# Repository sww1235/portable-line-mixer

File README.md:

# portable-line-mixer
A compact line level audio mixer.

Volume control via Digipots.

## TODO

-   Export BOM and price out parts
-   CODE

## Extra parts

-   772-E25-103RYY1 norcomp db25 IP67 connector male
-   772-E25-203RYY1 norcomp db25 IP67 connector female (for panelmount)
-   967-025-010R011 norcomp db25 IP67 backshell for cable
-   SFP6725 norcomp adhesive seal db25 size
-   967-025-CAP norcomp ip67 sealing cap
-   160-067-004R034 norcomp db25 hardware kit
-   767KS1(X) 0.084 \[2.1\] id/od sealed locking power plug switchcraft
-   L722AS 0.08 \[2.0\] id/od sealed locking power jack switchcraft (these sizes are compatible with high amperage version)
-   JCAP  power jack cover
-   35FM3AULS - Sealed locking 3.5mm panel mount jack switchcraft
-   35HDLBAU(S) 3.5mm sealed locking plug switchcraft (S=0.175 diameter cable, no S=0.29 diameter cable)
-   NE8FDX-P6-W IP rated ethercon connector Cat6A shielded neutrik
-   NE8MX6 Cat6A ethercon cable connector neutrik

## Max Power Consumption figures

| Component | Quantity | Current  | Voltage    | Total Watts     |
|:----------|:---------|:---------|:-----------|:----------------|
| 4x Op Amp | 1        | 2.8mA    | ±12V       | 67.2mW          |
| digipots  | 8        | 2uA, 5uA | +5VD, ±5VA | 0.48mW -> 0.5mW |
| microproc | 1        | 27mA     | 5V         | 135mW           |
| Total     |          |          |            | 202.68mW        |
| ref total |          |          |            | 500mW           |

## References / sources

### Code
-   <http://playground.arduino.cc/Main/RotaryEncoders#Example1>
-   <https://www.arduino.cc/en/Reference/Wire>
-   <http://gammon.com.au/interrupts>
-   <https://www.arduino.cc/en/Reference/AttachInterrupt>

### Physical Design
-   <https://m.reddit.com/r/arduino/comments/1tr7in/question_i_burned_out_this_small_smd_component_on/>
-   <https://www.arduino.cc/en/Hacking/PinMapping32u4>
-   <https://www.arduino.cc/en/Main/ArduinoBoardMicro>
-   <http://www.atmel.com/Images/Atmel-7766-8-bit-AVR-ATmega16U4-32U4_Datasheet.pdf>
-   <http://sound.whsites.net/articles/capacitors.htm>
-   <http://electronics.stackexchange.com/questions/210376/details-on-pcb-layout-for-microcontroller>
-   <http://electronics.stackexchange.com/questions/210580/pcb-microcontroller-layout-in-a-mixed-signal-system>
-   <http://electronics.stackexchange.com/questions/7535/what-precautions-should-i-take-when-mixing-analog-audio-and-digital-on-the-same>
-   <https://wiki.xtronics.com/index.php/Eeschema#Printing_to_a_web_viewable_file>
-   <http://www.all-electric.com/schematic/simp_mix.htm>
-   <http://sound.whsites.net/articles/audio-mixing.htm>
-   <http://www.hobbyprojects.com/A/mixers.html>
-   <https://www.maximintegrated.com/en/app-notes/index.mvp/id/1133>
-   <https://books.google.com/books?id=rZDbnQ0siCYC&pg=PA65&lpg=PA65&dq=max6820+capacitor+value&source=bl&ots=sMOHEXxgaR&sig=d1sH1XYZMVvH4Y1nVS2bvKtejF0&hl=en&sa=X&ved=0ahUKEwic_NTY_e3PAhXBx4MKHRdlA-UQ6AEIRTAH#v=onepage&q=max6820%20capacitor%20value&f=false>
-   <http://electronics.stackexchange.com/questions/5403/standard-pcb-trace-widths>
-   <http://electronics.stackexchange.com/questions/185212/i2c-pcb-layout-considerations>
-   <http://electronics.stackexchange.com/questions/39136/competing-pcb-crystal-layout-recommendations>
-   <http://electronics.stackexchange.com/questions/41851/how-critical-is-the-layout-of-usb-data-lines-how-does-my-layout-look>
-   <http://www.atmel.com/Images/Atmel-8128-Best-Practices-for-the-PCB-Layout-of-Oscillators_ApplicationNote_AVR186.pdf>
-   <http://www.ti.com/lit/an/scaa082/scaa082.pdf>
-   <http://electronics.stackexchange.com/questions/15135/decoupling-caps-pcb-layout/>
-   <http://electronics.stackexchange.com/questions/117817/learning-pcb-layout-strategy>
-   <http://electronics.stackexchange.com/questions/216410/pcb-layout-needs-improvement>
-   <http://electronics.stackexchange.com/questions/28251/rules-and-guidelines-for-drawing-good-schematics>
-   <http://electronics.stackexchange.com/questions/20180/pcb-layout-questions-for-mcu-breakout-board>
-   <http://electronics.stackexchange.com/questions/19688/is-it-normal-to-have-a-rats-nest-of-vcc-gnd-traces-under-an-ic>
-   <http://www.onmyphd.com/?p=pcb.design>
-   <http://www.ti.com/lit/an/scaa048/scaa048.pdf>
-   <http://www.hottconsultants.com/questions/mixed-signal_PCB_layout.html>
-   <http://www.hottconsultants.com/questions/supplying_power_to_a_mixed-signal_PCB.html>
-   <http://www.analog.com/en/analog-dialogue/articles/staying-well-grounded.html>

### Microphone references for future iterations of design
-   <http://electronics.stackexchange.com/questions/141499/5v-electret-microphone-to-pc-mute-switch-pop-help>

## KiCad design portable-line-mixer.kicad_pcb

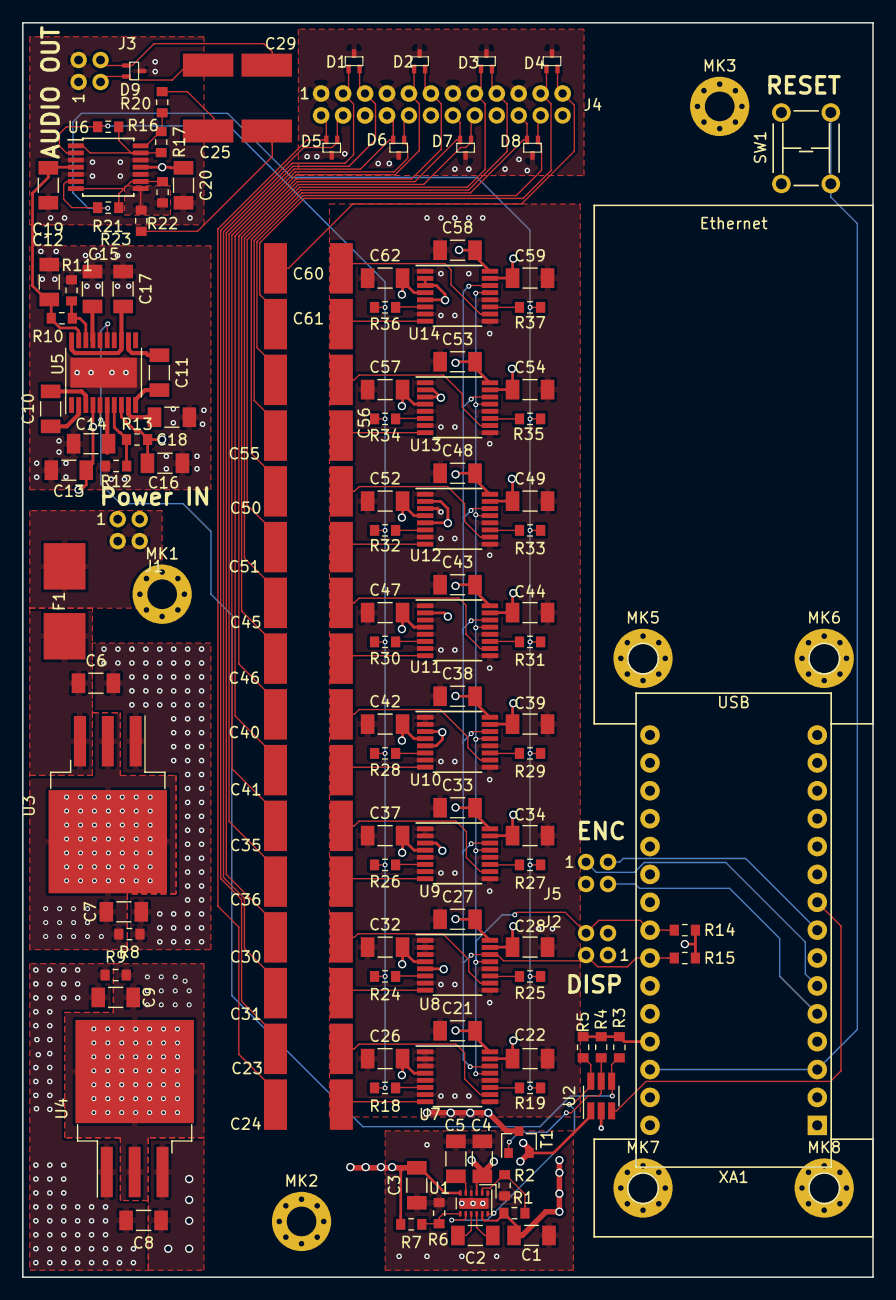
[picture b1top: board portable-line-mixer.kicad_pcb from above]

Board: 4 copper layers, 77.5 x 114.3 mm, 138 parts (0 on the bottom side), 93 nets.

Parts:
C1, C3: 2u2F; C_1206_3216Metric_Pad1.24x1.80mm_HandSolder
C2: 0.47uF; C_1206_3216Metric_Pad1.24x1.80mm_HandSolder
C4, C5: 4u7F; C_1206_3216Metric_Pad1.24x1.80mm_HandSolder
C6, C7, C8, C9, C12, C13, C16, C17, C18: 10uF; C_1206_3216Metric_Pad1.24x1.80mm_HandSolder
C10, C11: 1uF; C_1206_3216Metric_Pad1.24x1.80mm_HandSolder
C14, C15: 100nF; C_1206_3216Metric_Pad1.24x1.80mm_HandSolder
C19, C20: 0u1F; C_1206_3216Metric_Pad1.24x1.80mm_HandSolder
C21, C22, C26, C27, C28, C32, C33, C34, C37, C38, C39, C42, C43, C44, C47, C48, C49, C52, C53, C54, C57, C58, C59, C62: 0u01F; C_1206_3216Metric_Pad1.24x1.80mm_HandSolder
C23, C24, C25, C29, C30, C31, C35, C36, C40, C41, C45, C46, C50, C51, C55, C56, C60, C61: 1uF; Kemet_CAP_2220_5750Metric_D
D1, D2, D3, D4, D5, D6, D7, D8, D9: 0582BQ; SC-75_3L
F1: 5A; NANO-0154-OMNI-BLOK-Fuse-Holder
J1: Power In (Male-top); DF11-4DP-2DSA
J2: LCD Connection I2C; DF11-4DP-2DSA
J3: Audio Out; DF11-4DP-2DSA
J4: Audio IN; DF11-24DP-2DSA
J5: Encoder Connection; DF11-4DP-2DSA
MK1, MK2, MK3, MK5, MK6, MK7, MK8: Mounting_Hole_PAD; MountingHole_2.7mm_M2.5_Pad_Via
R1, R7: 220kΩ; R_0603_1608Metric_Pad0.84x1.00mm_HandSolder
R2, R6: 68kΩ; R_0603_1608Metric_Pad0.84x1.00mm_HandSolder
R3, R4, R5: 100kΩ; R_0603_1608Metric_Pad0.84x1.00mm_HandSolder
R8, R9: 1.3Ω; R_0603_1608Metric_Pad0.84x1.00mm_HandSolder
R10, R13: 681kΩ; R_0603_1608Metric_Pad0.84x1.00mm_HandSolder
R11, R12: 75kΩ; R_0603_1608Metric_Pad0.84x1.00mm_HandSolder
R14, R15: 4k7; R_0603_1608Metric_Pad0.84x1.00mm_HandSolder
R16, R17, R18, R19, R21, R22, R24, R25, R26, R27, R28, R29, R30, R31, R32, R33, R34, R35, R36, R37: 10k; R_0603_1608Metric_Pad0.84x1.00mm_HandSolder
R20, R23: 100R; R_0603_1608Metric_Pad0.84x1.00mm_HandSolder
SW1: Nano Reset; TL1105
T1: PMV45EN2; SOT-23
U1: LM27762; WSON-12-1EP_3x2mm_P0.5mm
U2: LM3880; SOT-23-6_Handsoldering
U3: LM1085-12V; TO-263-3_TabPin4
U4: LM1085-5V; TO-263-3_TabPin4
U5: LTC3265; TSSOP-20-1EP_4.4x6.5mm_P0.65mm_EP2.75x6.07mm-LTC3265
U6: OPA1604; TSSOP-14_4.4x5mm_P0.65mm
U7, U8, U9, U10, U11, U12, U13, U14: DS1882; TSSOP-16_4.4x5mm_P0.65mm
XA1: Nano_Headers; Nano-Header-Ethernet-4NANO

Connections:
+5V: C4.1, C9.1, J2.1, R3.1, R4.1, R5.1, R9.2, R14.1, R15.1, T1.2, U1.3, U2.1, U4.2, U4.4, XA1.27
+5VA: C1.1, C22.2, C28.2, C34.2, C39.2, C44.2, C49.2, C54.2, C59.2, R1.1, U1.11, U7.15, U8.15, U9.15, U10.15, U11.15, U12.15, U13.15, U14.15
+5VD: C21.2, C27.2, C33.2, C38.2, C43.2, C48.2, C53.2, C58.2, T1.3, U7.16, U8.5, U8.16, U9.3, U9.16, U10.3, U10.5, U10.16, U11.2, U11.16, U12.2, U12.5, U12.16, U13.2, U13.3, U13.16, U14.2, U14.3, U14.5, U14.16
+12V: C7.1, C8.1, C13.2, R8.2, U3.2, U3.4, U4.3, U5.4
+12VA: C12.2, C19.1, R10.1, U5.19, U6.4
-5VA: C3.2, C26.2, C32.2, C37.2, C42.2, C47.2, C52.2, C57.2, C62.2, R7.2, U1.6, U7.4, U8.4, U9.4, U10.4, U11.4, U12.4, U13.4, U14.4
-12VA: C16.1, C20.1, R13.2, U5.8, U6.11
/Arduino Nano Header Connections + Ethernet connection/5V-SCL: J2.3, R15.2, U7.14, U8.14, U9.14, U10.14, U11.14, U12.14, U13.14, U14.14, XA1.24
/Arduino Nano Header Connections + Ethernet connection/5V-SDA: J2.4, R14.2, U7.13, U8.13, U9.13, U10.13, U11.13, U12.13, U13.13, U14.13, XA1.23
/Arduino Nano Header Connections + Ethernet connection/Audio_Power_EN: U2.3, XA1.9
/Arduino Nano Header Connections + Ethernet connection/ENC-1: J5.1, XA1.6
/Arduino Nano Header Connections + Ethernet connection/ENC-A: J5.3, XA1.8
/Arduino Nano Header Connections + Ethernet connection/ENC-B: J5.4, XA1.5
/Arduino Nano Header Connections + Ethernet connection/Nano_RST: SW1.1, XA1.3, XA1.28
/Audio Mixer/F-LIN-0: C24.1, U7.8
/Audio Mixer/F-LIN-1: C31.1, U8.8
/Audio Mixer/F-LIN-2: C36.1, U9.8
/Audio Mixer/F-LIN-3: C41.1, U10.8
/Audio Mixer/F-LIN-4: C46.1, U11.8
/Audio Mixer/F-LIN-5: C51.1, U12.8
/Audio Mixer/F-LIN-6: C56.1, U13.8
/Audio Mixer/F-LIN-7: C61.1, U14.8
/Audio Mixer/F-RIN-0: C23.2, U7.10
/Audio Mixer/F-RIN-1: C30.2, U8.10
/Audio Mixer/F-RIN-2: C35.2, U9.10
/Audio Mixer/F-RIN-3: C40.2, U10.10
/Audio Mixer/F-RIN-4: C45.2, U11.10
/Audio Mixer/F-RIN-5: C50.2, U12.10
/Audio Mixer/F-RIN-6: C55.2, U13.10
/Audio Mixer/F-RIN-7: C60.2, U14.10
/Audio Mixer/L-IN0: C24.2, D5.2, J4.2
/Audio Mixer/L-IN1: C31.2, D1.1, J4.3
/Audio Mixer/L-IN2: C36.2, D6.2, J4.8
/Audio Mixer/L-IN3: C41.2, D2.1, J4.9
/Audio Mixer/L-IN4: C46.2, D7.2, J4.14
/Audio Mixer/L-IN5: C51.2, D3.1, J4.15
/Audio Mixer/L-IN6: C56.2, D8.2, J4.20
/Audio Mixer/L-IN7: C61.2, D4.1, J4.21
/Audio Mixer/LINV: R16.1, R17.2, U6.1, U6.13
/Audio Mixer/LOUT: C25.1, D9.2, J3.2
/Audio Mixer/LOUT-0: R18.1, U7.6
/Audio Mixer/LOUT-1: R24.1, U8.6
/Audio Mixer/LOUT-2: R26.1, U9.6
/Audio Mixer/LOUT-3: R28.1, U10.6
/Audio Mixer/LOUT-4: R30.1, U11.6
/Audio Mixer/LOUT-5: R32.1, U12.6
/Audio Mixer/LOUT-6: R34.1, U13.6
/Audio Mixer/LOUT-7: R36.1, U14.6
/Audio Mixer/L_MIX_BUS: R16.2, R18.2, R24.2, R26.2, R28.2, R30.2, R32.2, R34.2, R36.2, U6.2
/Audio Mixer/R-IN0: C23.1, D5.1, J4.4
/Audio Mixer/R-IN1: C30.1, D1.2, J4.5
/Audio Mixer/R-IN2: C35.1, D6.1, J4.10
/Audio Mixer/R-IN3: C40.1, D2.2, J4.11
/Audio Mixer/R-IN4: C45.1, D7.1, J4.16
/Audio Mixer/R-IN5: C50.1, D3.2, J4.17
/Audio Mixer/R-IN6: C55.1, D8.1, J4.22
/Audio Mixer/R-IN7: C60.1, D4.2, J4.23
/Audio Mixer/RINV: R21.1, R22.2, U6.7, U6.9
/Audio Mixer/ROUT: C29.1, D9.1, J3.4
/Audio Mixer/ROUT-0: R19.2, U7.11
/Audio Mixer/ROUT-1: R25.2, U8.11
/Audio Mixer/ROUT-2: R27.2, U9.11
/Audio Mixer/ROUT-3: R29.2, U10.11
/Audio Mixer/ROUT-4: R31.2, U11.11
/Audio Mixer/ROUT-5: R33.2, U12.11
/Audio Mixer/ROUT-6: R35.2, U13.11
/Audio Mixer/ROUT-7: R37.2, U14.11
/Audio Mixer/R_MIX_BUS: R19.1, R21.2, R25.1, R27.1, R29.1, R31.1, R33.1, R35.1, R37.1, U6.6
/Power Handling/+5VD_EN: R4.2, T1.1, U2.5
/Power Handling/+12V-F: C6.1, F1.2, U3.3
/Power Handling/ADJ+: R10.2, R11.1, U5.18
/Power Handling/ADJ-: R12.2, R13.1, U5.7
/Power Handling/BYP+: C15.1, U5.17
/Power Handling/BYP-: C14.2, U5.6
/Power Handling/CBST+: C10.2, U5.3
/Power Handling/CBST-: C10.1, U5.2
/Power Handling/CINV+: C11.2, U5.10
/Power Handling/CINV-: C11.1, U5.12
/Power Handling/VIN+: F1.1, J1.2, J1.4
/Power Handling/VOUT+: C17.2, U5.13, U5.20
/Power Handling/VOUT-: C18.2, U5.9
/Power Handling/±5VA_EN: R5.2, U1.8, U1.12, U2.6
/Power Handling/±12VA_EN: R3.2, U2.4, U5.5, U5.15
GNDREF: C1.2, C3.1, C4.2, C5.2, C6.2, C7.2, C8.2, C9.2, C12.1, C13.1, C14.1, C15.2, C16.2, C17.1, C18.1, C19.2, C20.2, C21.1, C22.1, C26.1, C27.1, C28.1, C32.1, C33.1, C34.1, C37.1, C38.1, C39.1, C42.1, C43.1, C44.1, C47.1, C48.1, C49.1, C52.1, C53.1, C54.1, C57.1, C58.1, C59.1, C62.1, D1.3, D2.3, D3.3, D4.3, D5.3, D6.3, D7.3, D8.3, D9.3, J1.1, J1.3, J2.2, J3.1, J3.3, J4.1, J4.6, J4.7, J4.12, J4.13, J4.18, J4.19, J4.24, J5.2, MK1.1, MK2.1, MK3.1, MK5.1, MK6.1, MK7.1, MK8.1, R2.2, R6.1, R8.1, R9.1, R11.2, R12.1, SW1.2, U1.1, U1.4, U1.13, U2.2, U3.1, U4.1, U5.14, U5.16, U5.21, U6.3, U6.5, U6.10, U6.12, U7.1, U7.2, U7.3, U7.5, U7.7, U7.9, U7.12, U8.1, U8.2, U8.3, U8.7, U8.9, U8.12, U9.1, U9.2, U9.5, U9.7, U9.9, U9.12, U10.1, U10.2, U10.7, U10.9, U10.12, U11.1, U11.3, U11.5, U11.7, U11.9, U11.12, U12.1, U12.3, U12.7, U12.9, U12.12, U13.1, U13.5, U13.7, U13.9, U13.12, U14.1, U14.7, U14.9, U14.12, XA1.4, XA1.29
unnamed: C2.1, U1.10
unnamed: C2.2, U1.9
unnamed: C5.1, U1.5
unnamed: C25.2, R20.1
unnamed: C29.2, R23.1
unnamed: R1.2, R2.1, U1.2
unnamed: R6.2, R7.1, U1.7
unnamed: R17.1, R20.2, U6.14
unnamed: R22.1, R23.2, U6.8

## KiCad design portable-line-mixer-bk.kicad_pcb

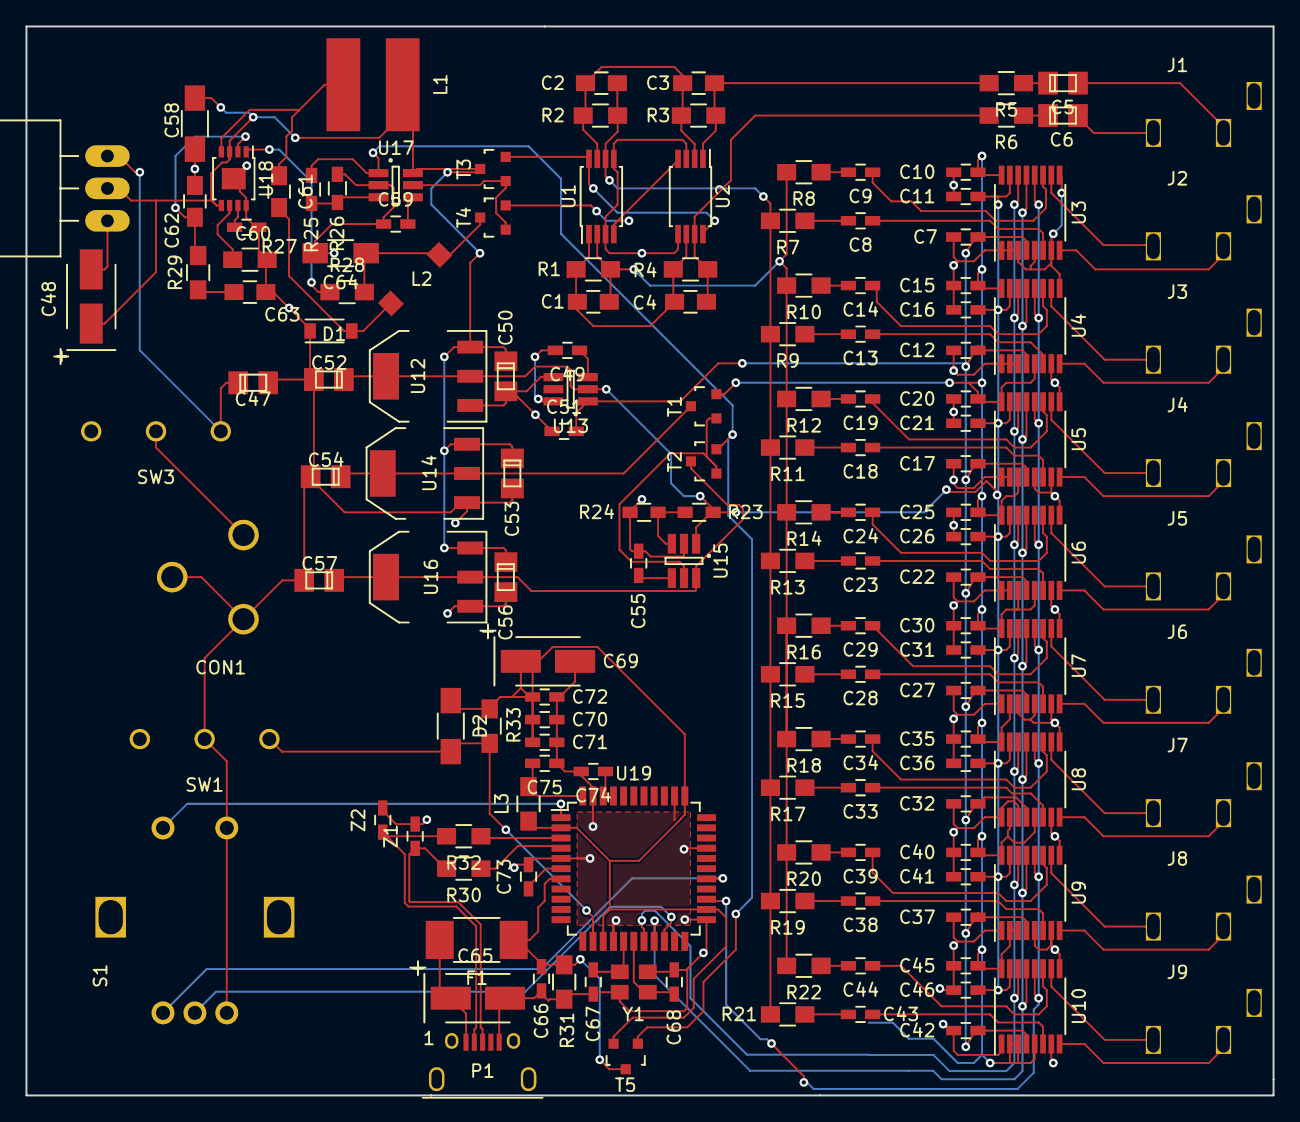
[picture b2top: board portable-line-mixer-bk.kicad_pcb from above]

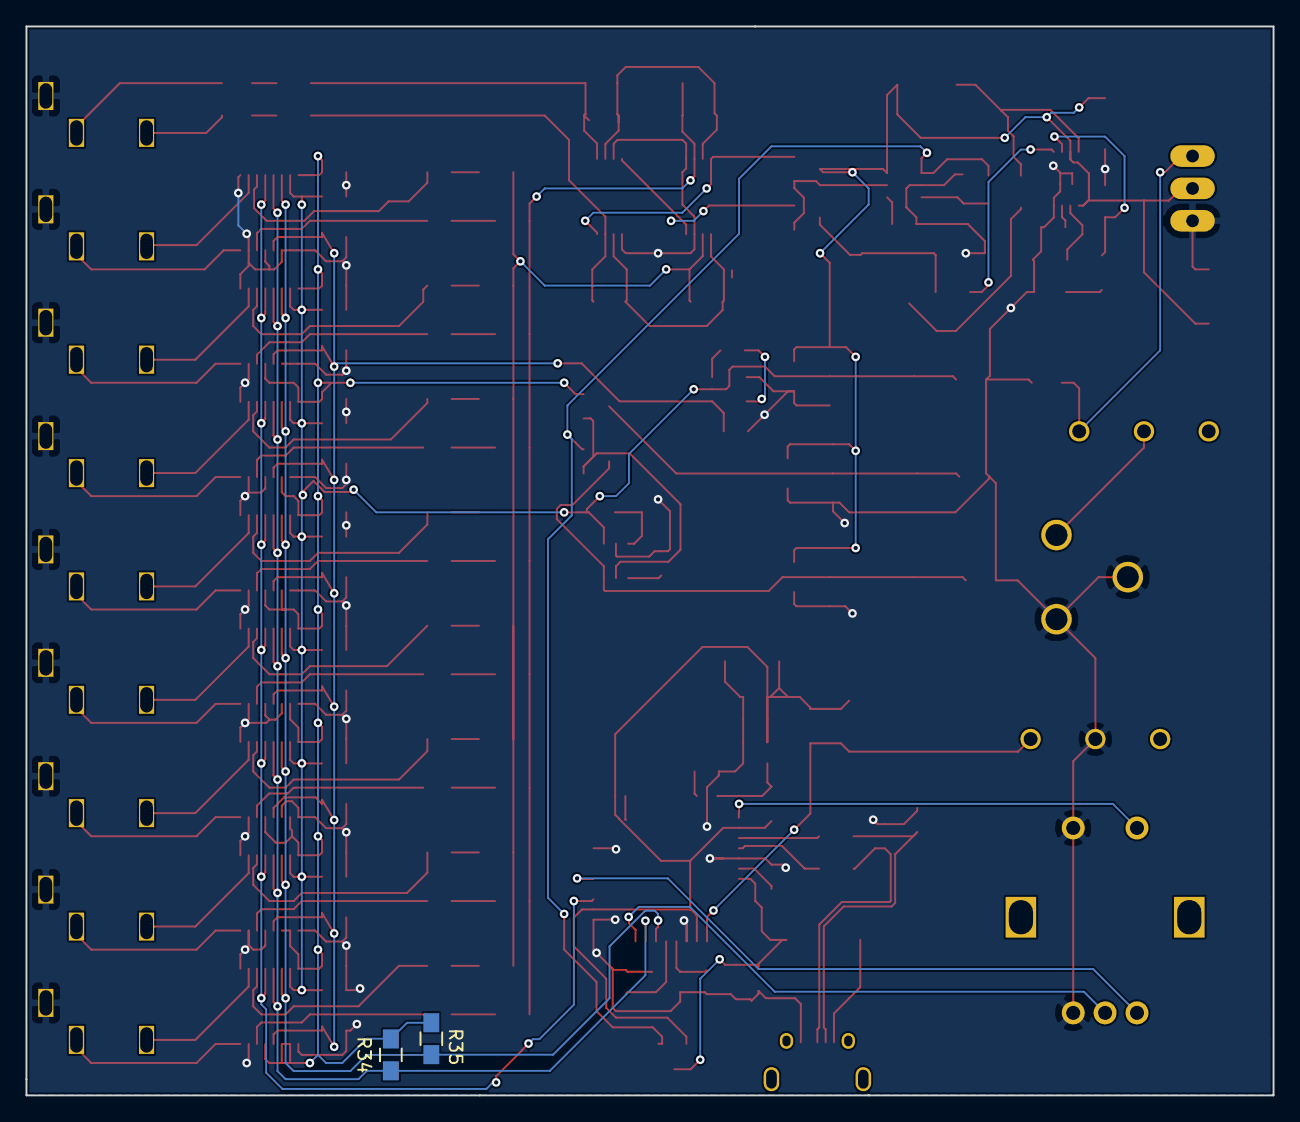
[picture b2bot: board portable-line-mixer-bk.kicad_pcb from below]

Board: 2 copper layers, 97.8 x 83.8 mm, 157 parts (2 on the bottom side), 105 nets.

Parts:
C1, C2: 27pF; C_0805_HandSoldering
C3, C4, C62: 47pF; C_0805_HandSoldering
C5, C6, C47, C50, C52, C53, C54, C56, C57: 10uF; TantalC_SizeR_EIA-2012
C7, C10, C11, C12, C15, C16, C17, C20, C21, C22, C25, C26, C27, C30, C31, C32, C35, C36, C37, C40, C41, C42, C45, C46, C55, C59: 0u01F; C_0603_HandSoldering
C8, C9, C13, C14, C18, C19, C23, C24, C28, C29, C33, C34, C38, C39, C43, C44, C49, C51, C73, C75: 1uF; C_0603_HandSoldering
C48, C65, C69: 22uF; TantalC_SizeB_EIA-3528_HandSoldering
C58: 2u2F; C_1206_HandSoldering
C60: 0u1F; C_0603_HandSoldering
C61: 1uF; C_0805_HandSoldering
C63: 2n2F; C_0805_HandSoldering
C64: 10uF; C_1206_HandSoldering
C66, C70, C71, C72, C74: 100nF; C_0603_HandSoldering
C67, C68: 22pF; C_0603_HandSoldering
CON1: BARREL_JACK; L712RAS
D1: CMMSH1-40; SOD-123
D2: CD1206-S01575; C_1206_HandSoldering
F1: MF-MSMF050-2; C_1812_HandSoldering
J1, J2, J3, J4, J5, J6, J7, J8, J9: JACK-TRS; SJ1-353XNG-3Pin
L1: 10uH; CDRH6D28
L2: 22uH; CDRH3D28NP
L3: MH2029-300Y; R_0805_HandSoldering
P1: USB_OTG; ZX62D-B-5PA8(30)
R1, R2, R3, R4, R7, R8, R9, R10, R11, R12, R13, R14, R15, R16, R17, R18, R19, R20, R21, R22, R29, R33: 10k; R_0805_HandSoldering
R5, R6: 100R; R_0805_HandSoldering
R23: 700R; R_0603_HandSoldering
R24, R26: 100R; R_0603_HandSoldering
R25: 630R; R_0603_HandSoldering
R27: 45k3; R_0805_HandSoldering
R28: 147k; R_0805_HandSoldering
R30, R31, R32: 22R; R_0805_HandSoldering
R34, R35: 4k7; C_0805_HandSoldering
S1: PEC11-4215F-S24; PEC11R-4xxx-Sxxxx
SW1: RESET; M7
SW3: ON/OFF; M7
T1, T2, T3, T4: PMV45EN2; SOT-23
T5: PMV48XP; SOT-23
U1, U2: RC4560; TSSOP-8_4.4x3mm_Pitch0.65mm
U3, U4, U5, U6, U7, U8, U9, U10: DS1882; TSSOP-16_4.4x5mm_Pitch0.65mm
U11: LT1085; TO-220_Neutral123_Horizontal_LargePads
U12, U14, U16: NCP1117ST50T3G_MountingTab; SOT-223
U13: MAX1721; SOT-23-6_Handsoldering
U15, U17: MAX6820; SOT-23-6_Handsoldering
U18: LT3580; MSOP-8-1EP_3x3mm_Pitch0.65mm
U19: ATMEGA32U4-A; TQFP-44_10x10mm_Pitch0.8mm
Y1: LFXTAL056036; CFPX-180
Z1, Z2: CG0603MLC-05E; C_0603_HandSoldering

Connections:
+5VA: C11.2, C16.2, C21.2, C26.2, C31.2, C36.2, C41.2, C46.2, C52.1, R23.1, U3.15, U4.15, U5.15, U6.15, U7.15, U8.15, U9.15, U10.15, U12.2, U12.4, U13.2, U15.1
+5VD: C10.2, C15.2, C20.2, C25.2, C30.2, C35.2, C40.2, C45.2, R34.2, R35.2, T1.2, U3.16, U4.5, U4.16, U5.3, U5.16, U6.3, U6.5, U6.16, U7.2, U7.16, U8.2, U8.5, U8.16, U9.2, U9.3, U9.16, U10.2, U10.3, U10.5, U10.16
+5VP: R25.1, T2.2, T5.1, U17.1
+12VA: T3.2, U1.8, U2.8
-5V: C7.1, C12.1, C17.1, C22.1, C27.1, C32.1, C37.1, C42.1, C51.2, U3.4, U4.4, U5.4, U6.4, U7.4, U8.4, U9.4, U10.4, U13.1
-12VA: T4.2, U1.4, U2.4
/Microprocessor/+5VARD: C69.1, C70.1, C71.1, C72.1, D2.1, L3.1, R33.1, T5.2, U19.2, U19.14, U19.24, U19.34
/Microprocessor/D+: P1.3, R30.2, Z1.1
/Microprocessor/D-: P1.2, R32.2, Z2.1
/Microprocessor/ENC-1: S1.1, U19.1
/Microprocessor/ENC-A: S1.3, U19.27
/Microprocessor/ENC-B: S1.5, U19.20
/Microprocessor/RESET: D2.2, R33.2, SW1.2, U19.13
/Microprocessor/USB-D+: R30.1, U19.4
/Microprocessor/USB-D-: R32.1, U19.3
/Microprocessor/VUSB: C66.1, F1.1, R31.2, T5.3, U19.7
/SCL: R35.1, U3.14, U4.14, U5.14, U6.14, U7.14, U8.14, U9.14, U10.14, U19.18
/SDA: R34.1, U3.13, U4.13, U5.13, U6.13, U7.13, U8.13, U9.13, U10.13, U19.19
/Stereo-Input-0/LEFT: J2.2, U3.8
/Stereo-Input-0/LOUT: C2.1, R2.2, R7.2, R9.2, R11.2, R13.2, R15.2, R17.2, R19.2, R21.2, U1.6
/Stereo-Input-0/RIGHT: J2.3, U3.10
/Stereo-Input-0/ROUT: C1.1, R1.2, R8.2, R10.2, R12.2, R14.2, R16.2, R18.2, R20.2, R22.2, U1.2
/Stereo-Input-1/LEFT: J3.2, U4.8
/Stereo-Input-1/RIGHT: J3.3, U4.10
/Stereo-Input-2/LEFT: J4.2, U5.8
/Stereo-Input-2/RIGHT: J4.3, U5.10
/Stereo-Input-3/LEFT: J5.2, U6.8
/Stereo-Input-3/RIGHT: J5.3, U6.10
/Stereo-Input-4/LEFT: J6.2, U7.8
/Stereo-Input-4/RIGHT: J6.3, U7.10
/Stereo-Input-5/LEFT: J7.2, U8.8
/Stereo-Input-5/RIGHT: J7.3, U8.10
/Stereo-Input-6/LEFT: J8.2, U9.8
/Stereo-Input-6/RIGHT: J8.3, U9.10
/Stereo-Input-7/LEFT: J9.2, U10.8
/Stereo-Input-7/RIGHT: J9.3, U10.10
/~CE: U3.12, U4.12, U5.12, U6.12, U7.12, U8.12, U9.12, U10.12, U19.25
GNDREF: C7.2, C10.1, C11.1, C12.2, C15.1, C16.1, C17.2, C20.1, C21.1, C22.2, C25.1, C26.1, C27.2, C30.1, C31.1, C32.2, C35.1, C36.1, C37.2, C40.1, C41.1, C42.2, C45.1, C46.1, C47.2, C48.2, C50.2, C51.1, C52.2, C53.2, C54.2, C55.1, C56.2, C57.2, C58.2, C59.1, C60.1, C62.2, C63.2, C64.2, C65.2, C66.2, C67.1, C68.2, C69.2, C70.2, C71.2, C72.2, C73.2, C74.2, C75.1, CON1.2, CON1.3, D1.1, J1.1, J2.1, J3.1, J4.1, J5.1, J6.1, J7.1, J8.1, J9.1, P1.5, R24.2, R26.2, R27.1, R31.1, S1.2, S1.4, SW1.1, U1.3, U1.5, U2.3, U2.5, U3.1, U3.2, U3.3, U3.5, U3.7, U3.9, U4.1, U4.2, U4.3, U4.7, U4.9, U5.1, U5.2, U5.5, U5.7, U5.9, U6.1, U6.2, U6.7, U6.9, U7.1, U7.3, U7.5, U7.7, U7.9, U8.1, U8.3, U8.7, U8.9, U9.1, U9.5, U9.7, U9.9, U10.1, U10.7, U10.9, U11.1, U12.1, U13.4, U14.1, U15.2, U16.1, U17.2, U18.8, U18.9, U19.5, U19.15, U19.23, U19.30, U19.35, U19.43, Y1.2, Y1.4, Z1.2, Z2.2
unnamed: C1.2, C4.1, R1.1, R4.2, U1.1, U2.6
unnamed: C2.2, C3.1, R2.1, R3.2, U1.7, U2.2
unnamed: C3.2, R3.1, R5.2, U2.1
unnamed: C4.2, R4.1, R6.2, U2.7
unnamed: C5.1, R5.1
unnamed: C5.2, J1.2
unnamed: C6.1, R6.1
unnamed: C6.2, J1.3
unnamed: C8.1, U3.6
unnamed: C8.2, R7.1
unnamed: C9.1, U3.11
unnamed: C9.2, R8.1
unnamed: C13.1, U4.6
unnamed: C13.2, R9.1
unnamed: C14.1, U4.11
unnamed: C14.2, R10.1
unnamed: C18.1, U5.6
unnamed: C18.2, R11.1
unnamed: C19.1, U5.11
unnamed: C19.2, R12.1
unnamed: C23.1, U6.6
unnamed: C23.2, R13.1
unnamed: C24.1, U6.11
unnamed: C24.2, R14.1
unnamed: C28.1, U7.6
unnamed: C28.2, R15.1
unnamed: C29.1, U7.11
unnamed: C29.2, R16.1
unnamed: C33.1, U8.6
unnamed: C33.2, R17.1
unnamed: C34.1, U8.11
unnamed: C34.2, R18.1
unnamed: C38.1, U9.6
unnamed: C38.2, R19.1
unnamed: C39.1, U9.11
unnamed: C39.2, R20.1
unnamed: C43.1, U10.6
unnamed: C43.2, R21.1
unnamed: C44.1, U10.11
unnamed: C44.2, R22.1
unnamed: C47.1, SW3.2, U11.3
unnamed: C48.1, C50.1, C53.1, C56.1, C58.1, L1.1, T3.3, U11.2, U12.3, U14.3, U16.3, U17.6, U18.3, U18.5
unnamed: C49.1, U13.3
unnamed: C49.2, U13.6
unnamed: C54.1, T1.3, U14.2, U14.4
unnamed: C55.2, U15.4
unnamed: C57.1, T2.3, U15.6, U16.2, U16.4
unnamed: C59.2, U17.4
unnamed: C60.2, U18.7
unnamed: C61.1, L1.2, U18.4
unnamed: C61.2, D1.2, L2.1
unnamed: C62.1, R29.1, U18.2
unnamed: C63.1, R29.2
unnamed: C64.1, L2.2, R28.2, T4.3
unnamed: C65.1, F1.2, P1.1
unnamed: C67.2, U19.16, Y1.3
unnamed: C68.1, U19.17, Y1.1
unnamed: C73.1, U19.6
unnamed: C74.1, U19.42
unnamed: C75.2, L3.2, U19.44
unnamed: CON1.1, SW3.1
unnamed: R23.2, R24.1, U15.3
unnamed: R25.2, R26.1, U17.3
unnamed: R27.2, U18.6
unnamed: R28.1, U18.1
unnamed: T1.1, T2.1, U15.5
unnamed: T3.1, T4.1, U17.5

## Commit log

2016-10-22 almost done with first iteration of design
2016-10-22 finished with first draft of schematic
2016-10-30 finalized schematic, finishing footprint assignment, starting pcb layout
2016-10-30 replacing audio jack footprints
2016-10-30 before initial DRC
2016-10-30 after DRC and fixes
2016-11-02 added library reference table
2016-11-02 added references to readme
2016-11-08 added power consumption figures
2017-03-26 Add todo on readme
2017-03-31 updating to new kicad version
2017-03-31 adding library cache and recovery after new kicad version
2017-03-31 library updates for new kicad version 4.0.6
2017-03-31 Added USBC switchover to TODO list
2017-03-31 Create LICENSE
2017-12-27 Updated to new file formats
2018-04-01 Reworking with new power supply and layout
    also changing to kicad 5 style library layout and management
2018-04-02 Updated Schematics
    - added ethernet
    - swapped to using prebuilt nano
    - swapped to using db25 connector
    - swapped other connectors
    - added connectors for an LCD screen
2018-04-02 Added net labels and started schematic
2018-04-02 Removing old files from old design
2018-04-02 Swapped encoder for connector
2018-04-03 Portable Line Mixer done
2018-04-03 Fixed pad connection on ±12V regulator
2018-04-05 Swapped right angle reset switch for straight
2018-04-05 Exporting design reference files
2018-04-05 updating readme
2018-04-05 Updated power table
